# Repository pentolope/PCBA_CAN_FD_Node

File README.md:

# CAN-FD Sensor/Control Node

General-purpose CAN-FD node for a 24 V industrial system: MCU with CAN-FD, external transceiver, switchable termination, four inputs, four low-side outputs.

This repository holds the design problem for `PCBA_CAN_FD_Node`, titled in metadata "CAN-FD Sensor/Control Node": a general-purpose CAN-FD node for a 24 V industrial system. The brief fixes the functional skeleton: a modern MCU with CAN-FD driving an external CAN-FD transceiver, switchable 120-ohm bus termination, ESD protection at the bus connector, reverse-polarity and transient protection on the 24 V input, an efficient local regulator, and four digital inputs plus four low-side outputs for demonstration loads. It also fixes one placement rule — the CAN connector must place CANH/CANL adjacent, with protection and termination kept near that connector. Everything else is open: no part, vendor, connector, package, regulator topology, rail voltage, bit rate, current rating, board outline, or stackup is named, and the layer count is only characterised in metadata as "2 or 4". The design agent must choose and justify those, documenting engineering decisions rather than treating them as pre-existing user requirements.

> **This board has not been designed.** There is no schematic, no layout and no
> part selection here — only the brief, a reading of the brief, and the
> scaffolding a design run needs. That is the intended state of this repository,
> not a gap in it.

## What the brief fixes, and what it leaves open

The brief pins down 14 requirements and deliberately leaves
20 decisions to whoever designs the board. The `Source` column says
which is which: `brief` is quoted from [BRIEF.md](BRIEF.md), `metadata` comes
from the benchmark catalogue, and `open` means the brief does not fix it.

| Aspect | Value | Source |
|---|---|---|
| Board identity | repo PCBA_CAN_FD_Node; title "CAN-FD Sensor/Control Node"; benchmark_id 6 | metadata |
| Board function | General-purpose CAN-FD node for a 24 V industrial system | brief |
| Category / difficulty / brief detail | industrial-network; difficulty 2/5; detail 3/5 | metadata |
| Likely layer count | 2 or 4 | metadata |
| Primary stressors | CAN differential pair, 24V input protection, termination, MCU clocking | metadata |
| Controller | A modern MCU with CAN-FD (no family, part or package named) | brief |
| Bus PHY | External CAN-FD transceiver, separate from the MCU | brief |
| Bus termination | Switchable 120-ohm termination | brief |
| Bus protection | ESD protection at the bus connector | brief |
| 24 V input protection | Reverse-polarity and transient protection on the 24 V input | brief |
| Local power conversion | An efficient local regulator (topology, input source, rails and ratings unstated) | brief |
| Digital inputs | Four | brief |
| Outputs | Four low-side outputs, for demonstration loads | brief |
| CAN connector arrangement and protection zone | CANH/CANL adjacent at the connector; protection and termination kept near the connector | brief |
| Board outline, connector types, rails, bit rates and specific part numbers | Not fixed by the brief - design agent's choice | open |

The full split, with the verbatim brief text substantiating every fixed
requirement, is in [board/requirements.md](board/requirements.md) and
machine-readably in [board/requirements.json](board/requirements.json).

**Missing details are design freedom, not permission to fabricate unstated user
requirements.** A choice the brief left open is recorded as a decision, with its
reasoning — never promoted into a requirement.

## Benchmark position

| | |
|---|---|
| Benchmark id | 6 of 32 |
| Category | industrial-network |
| Difficulty | 2 / 5 |
| Brief detail | 3 / 5 |
| Likely layer count | 2 or 4 |
| Primary stressors | CAN differential pair, 24V input protection, termination, MCU clocking |

At difficulty 2/5 and brief detail 3/5 in the `industrial-network` category, this board tests whether an agent can execute a well-understood industrial node without over-claiming: the named stressors are the CAN differential pair, 24 V input protection, termination, and MCU clocking. The brief is specific about block-level content and one connector-region placement rule, but deliberately silent on parts, rails, bit rates, ratings, geometry and stackup — so the benchmark measures how cleanly an agent separates the stated architecture from the many unstated choices, and whether it can substantiate a differential pair, a protection front end, and a clock accurate enough for CAN-FD bit timing with real evidence rather than assertion.

This repository is one of thirty-two. The suite, the protocol and the results
live in [PCBA_AutoDesignAndTest_Bench](https://github.com/pentolope/PCBA_AutoDesignAndTest_Bench).

## Repository layout

| Path | Contents |
|---|---|
| `BRIEF.md` | the supplied brief — authoritative, preserved byte for byte, never edited |
| `board/requirements.md` | what the brief fixes, what it leaves open, and where decisions get recorded |
| `board/requirements.json` | the same split, machine-readable, each fixed requirement bound to brief text |
| `board/manifest.template.json` | the toolkit's minimum manifest, pre-filled for this board |
| `board/toolchain.json` | where this board's build finds KiCad and the router |
| `benchmark/metadata.json` | the supplied catalogue entry — category, difficulty, detail, stressors |
| `docs/architecture.md` | the decisions this board must make, as questions, unanswered |
| `docs/sources.md` | the classes of evidence the design will have to cite |
| `docs/status.md` | what exists, what does not, and what is deliberately absent |
| `candidates/` | disposable search output, ignored by Git |
| `.claude/skills/` | the accountability-review skill [CLAUDE.md](CLAUDE.md) requires before a push |
| `tooling/PCBA_AutoDesignAndTest` | the shared verification/routing/release toolkit, as a pinned submodule |

## Getting the repository

The toolkit is a submodule and carries KiCad Routing Tools as a submodule of its
own, so clone recursively:

```bash
git clone --recursive https://github.com/pentolope/PCBA_CAN_FD_Node.git
```

```bash
git submodule update --init --recursive
```

## Designing the board

Generic verification, routing and release logic is **not** written here. It is
consumed from `tooling/PCBA_AutoDesignAndTest`, which is board-agnostic by
construction and must stay that way; this repository owns the board and nothing
else. Start from
[the toolkit's onboarding guide](tooling/PCBA_AutoDesignAndTest/examples/onboarding.md),
and see [CLAUDE.md](CLAUDE.md) for the rules a design run works under.

```bash
python3 tooling/PCBA_AutoDesignAndTest/run.py preflight
```

## Brief integrity

`BRIEF.md` SHA-256 `3897ccfaae068a75cbd3eae3186d01ac4c7f7dafd298f4a1a979556b659bc86c`

Every quotation in `board/requirements.json` is bound to those exact bytes. If
the brief ever changes, the bindings are stale by construction — which is the
point of recording the digest.

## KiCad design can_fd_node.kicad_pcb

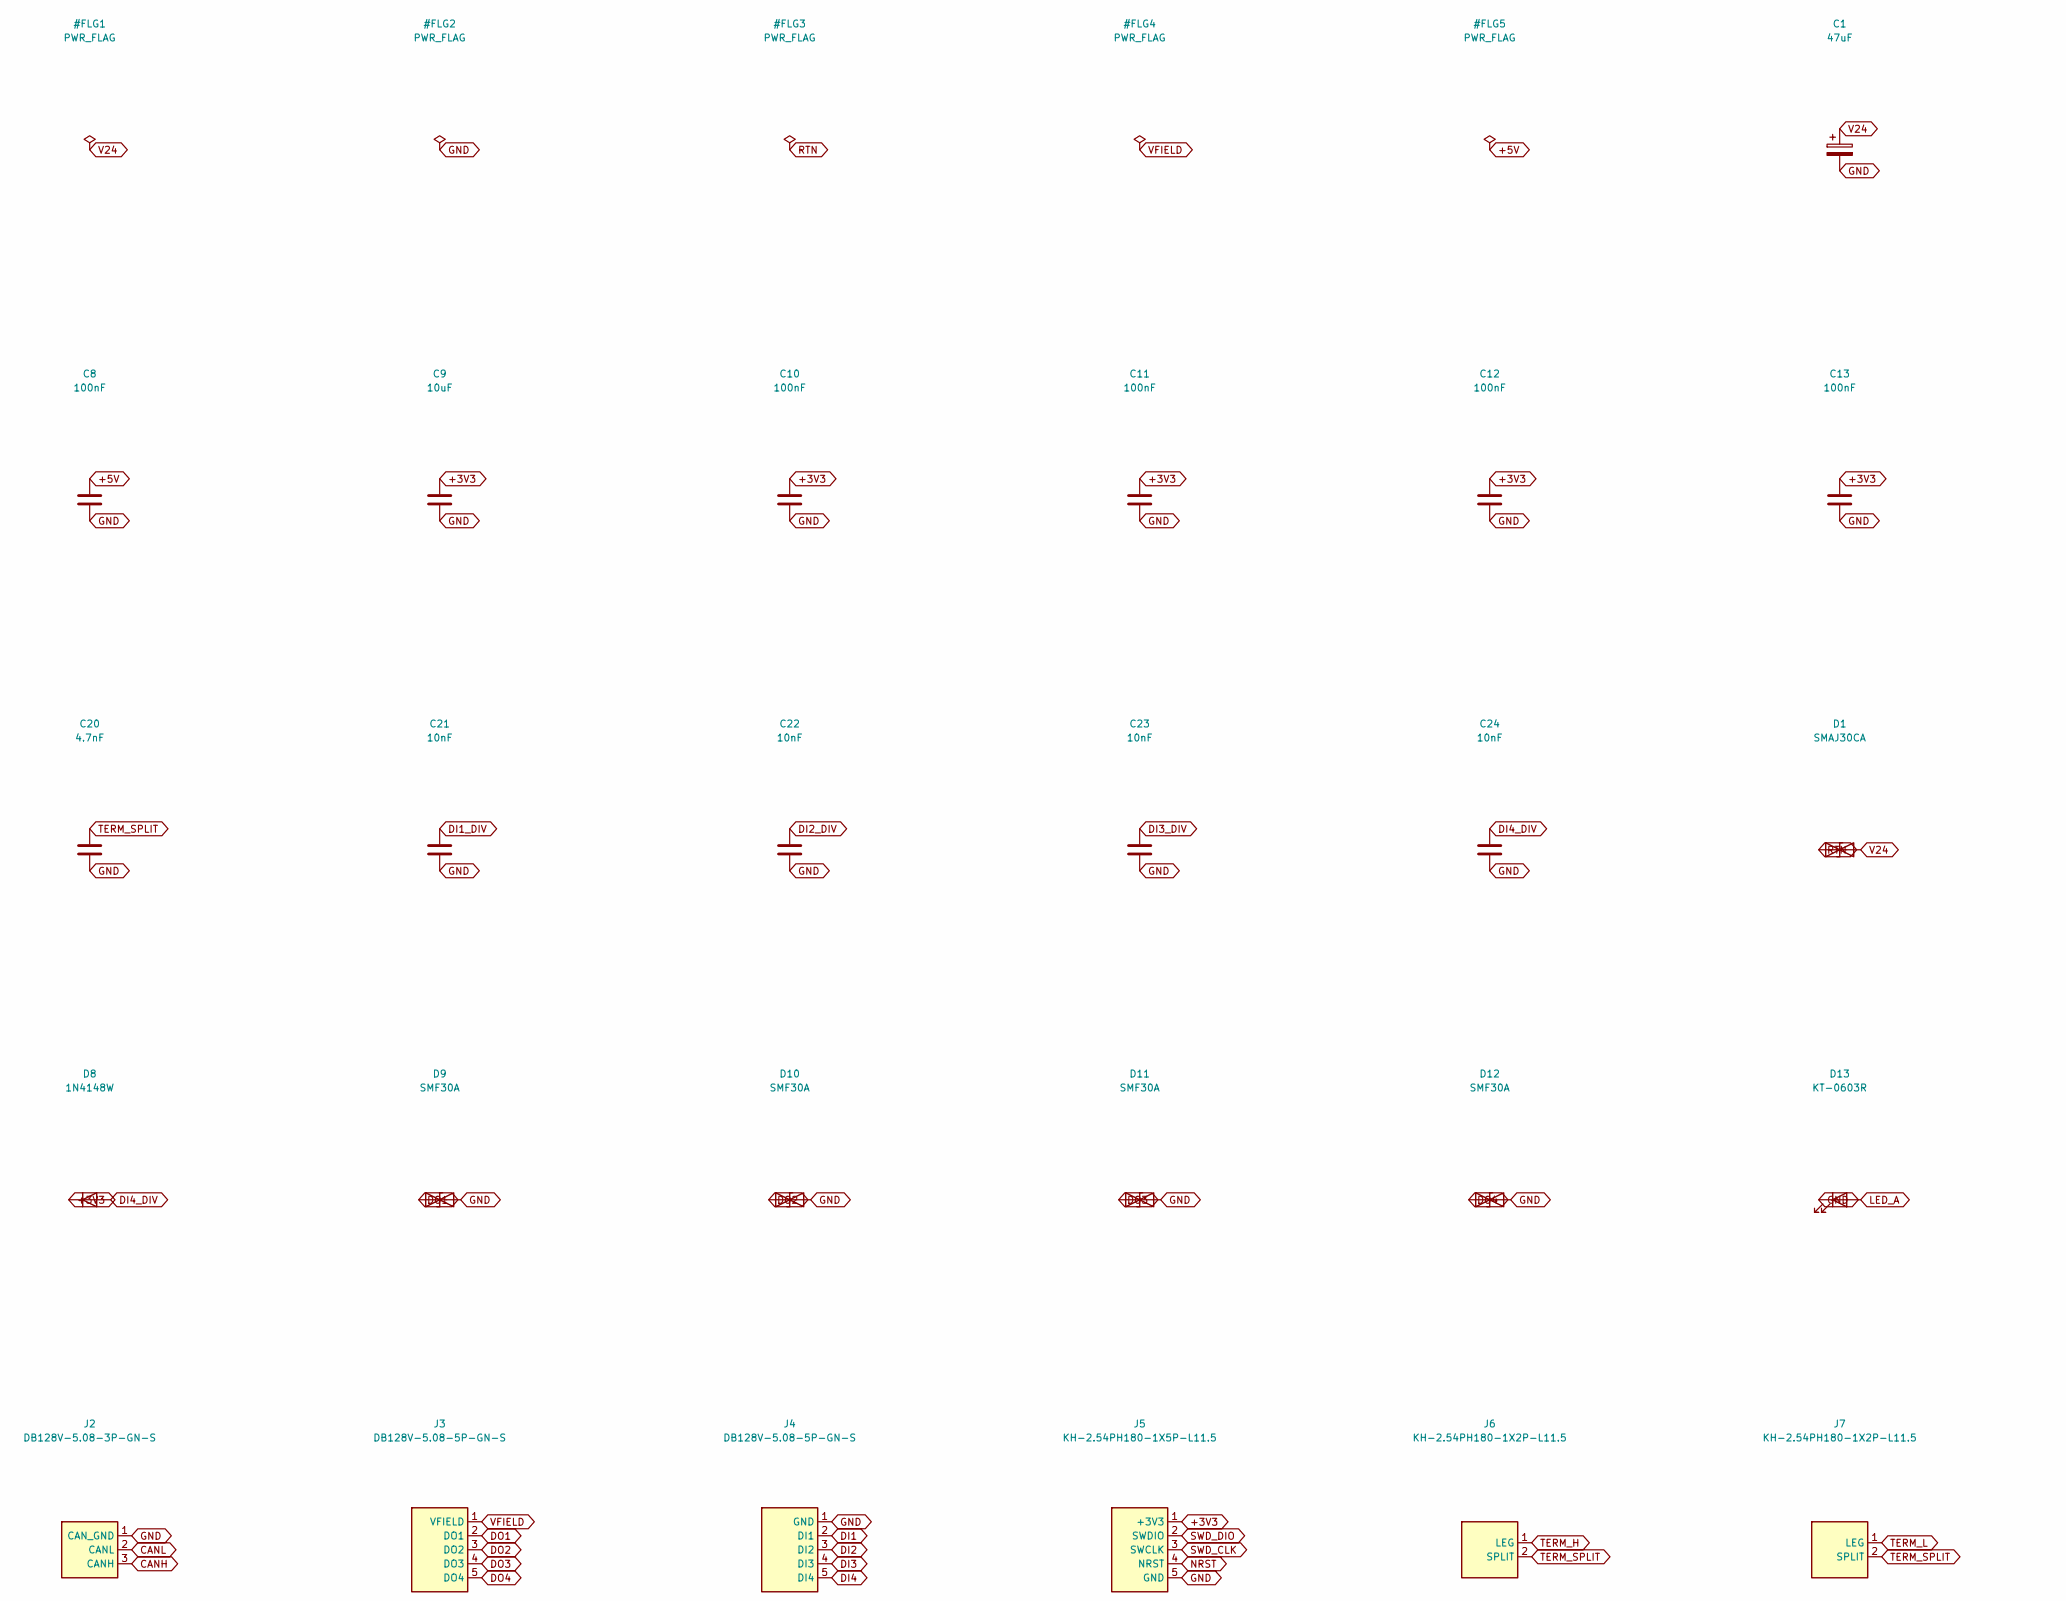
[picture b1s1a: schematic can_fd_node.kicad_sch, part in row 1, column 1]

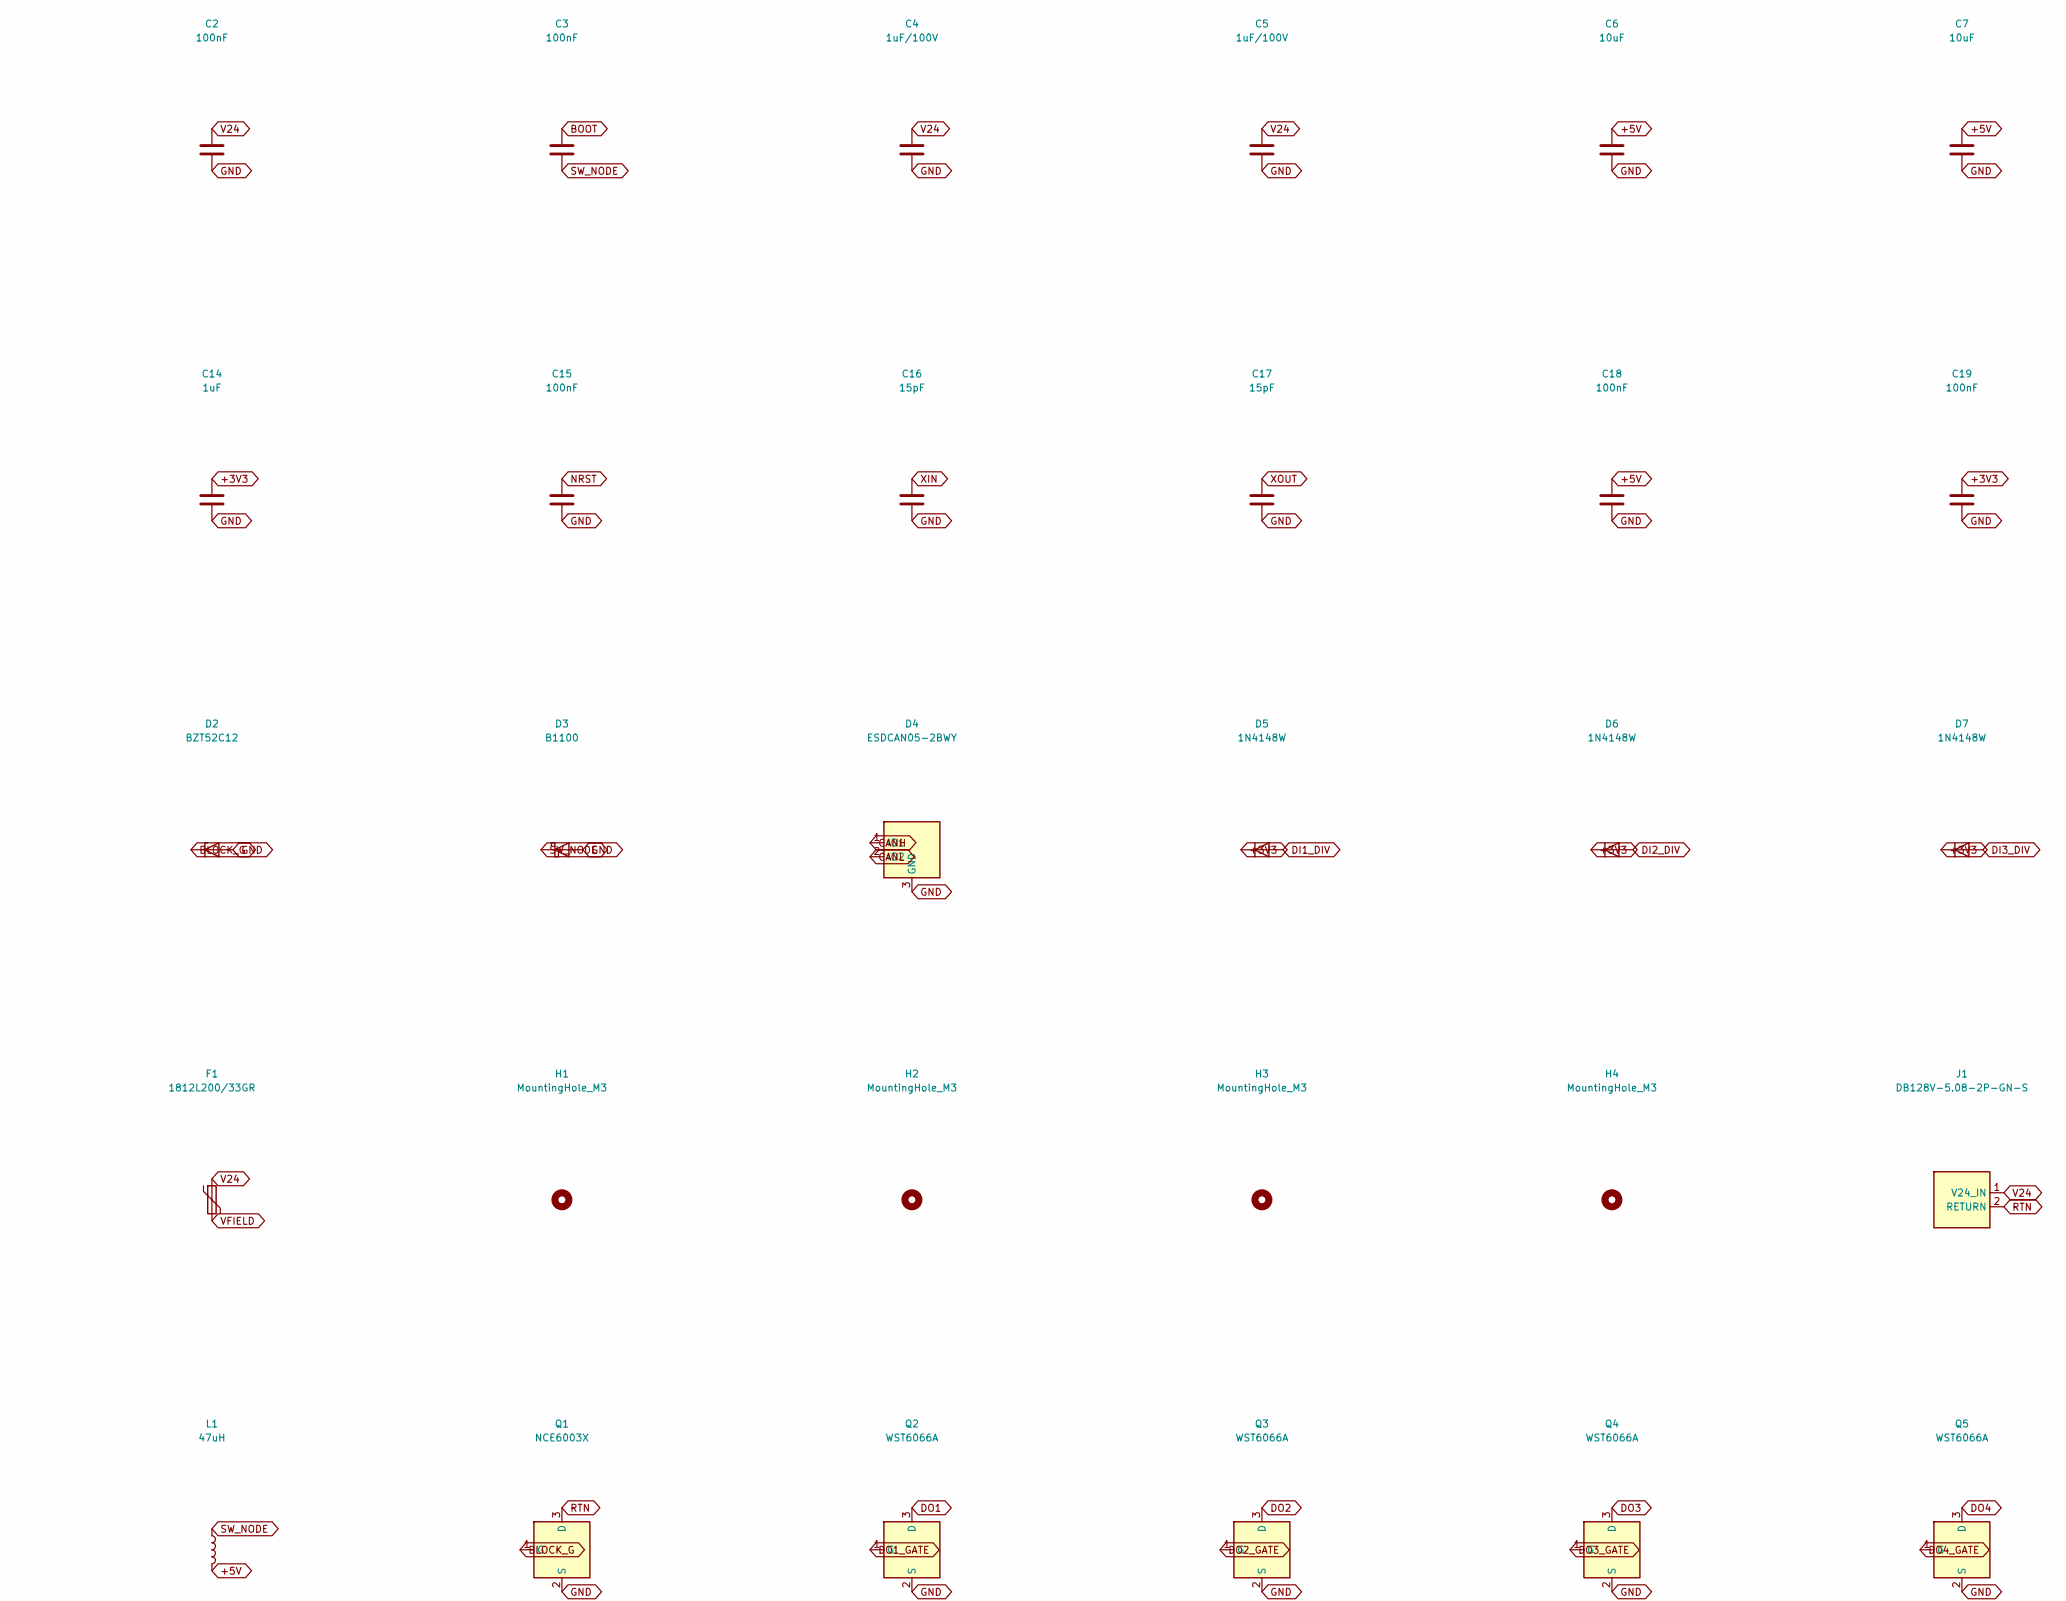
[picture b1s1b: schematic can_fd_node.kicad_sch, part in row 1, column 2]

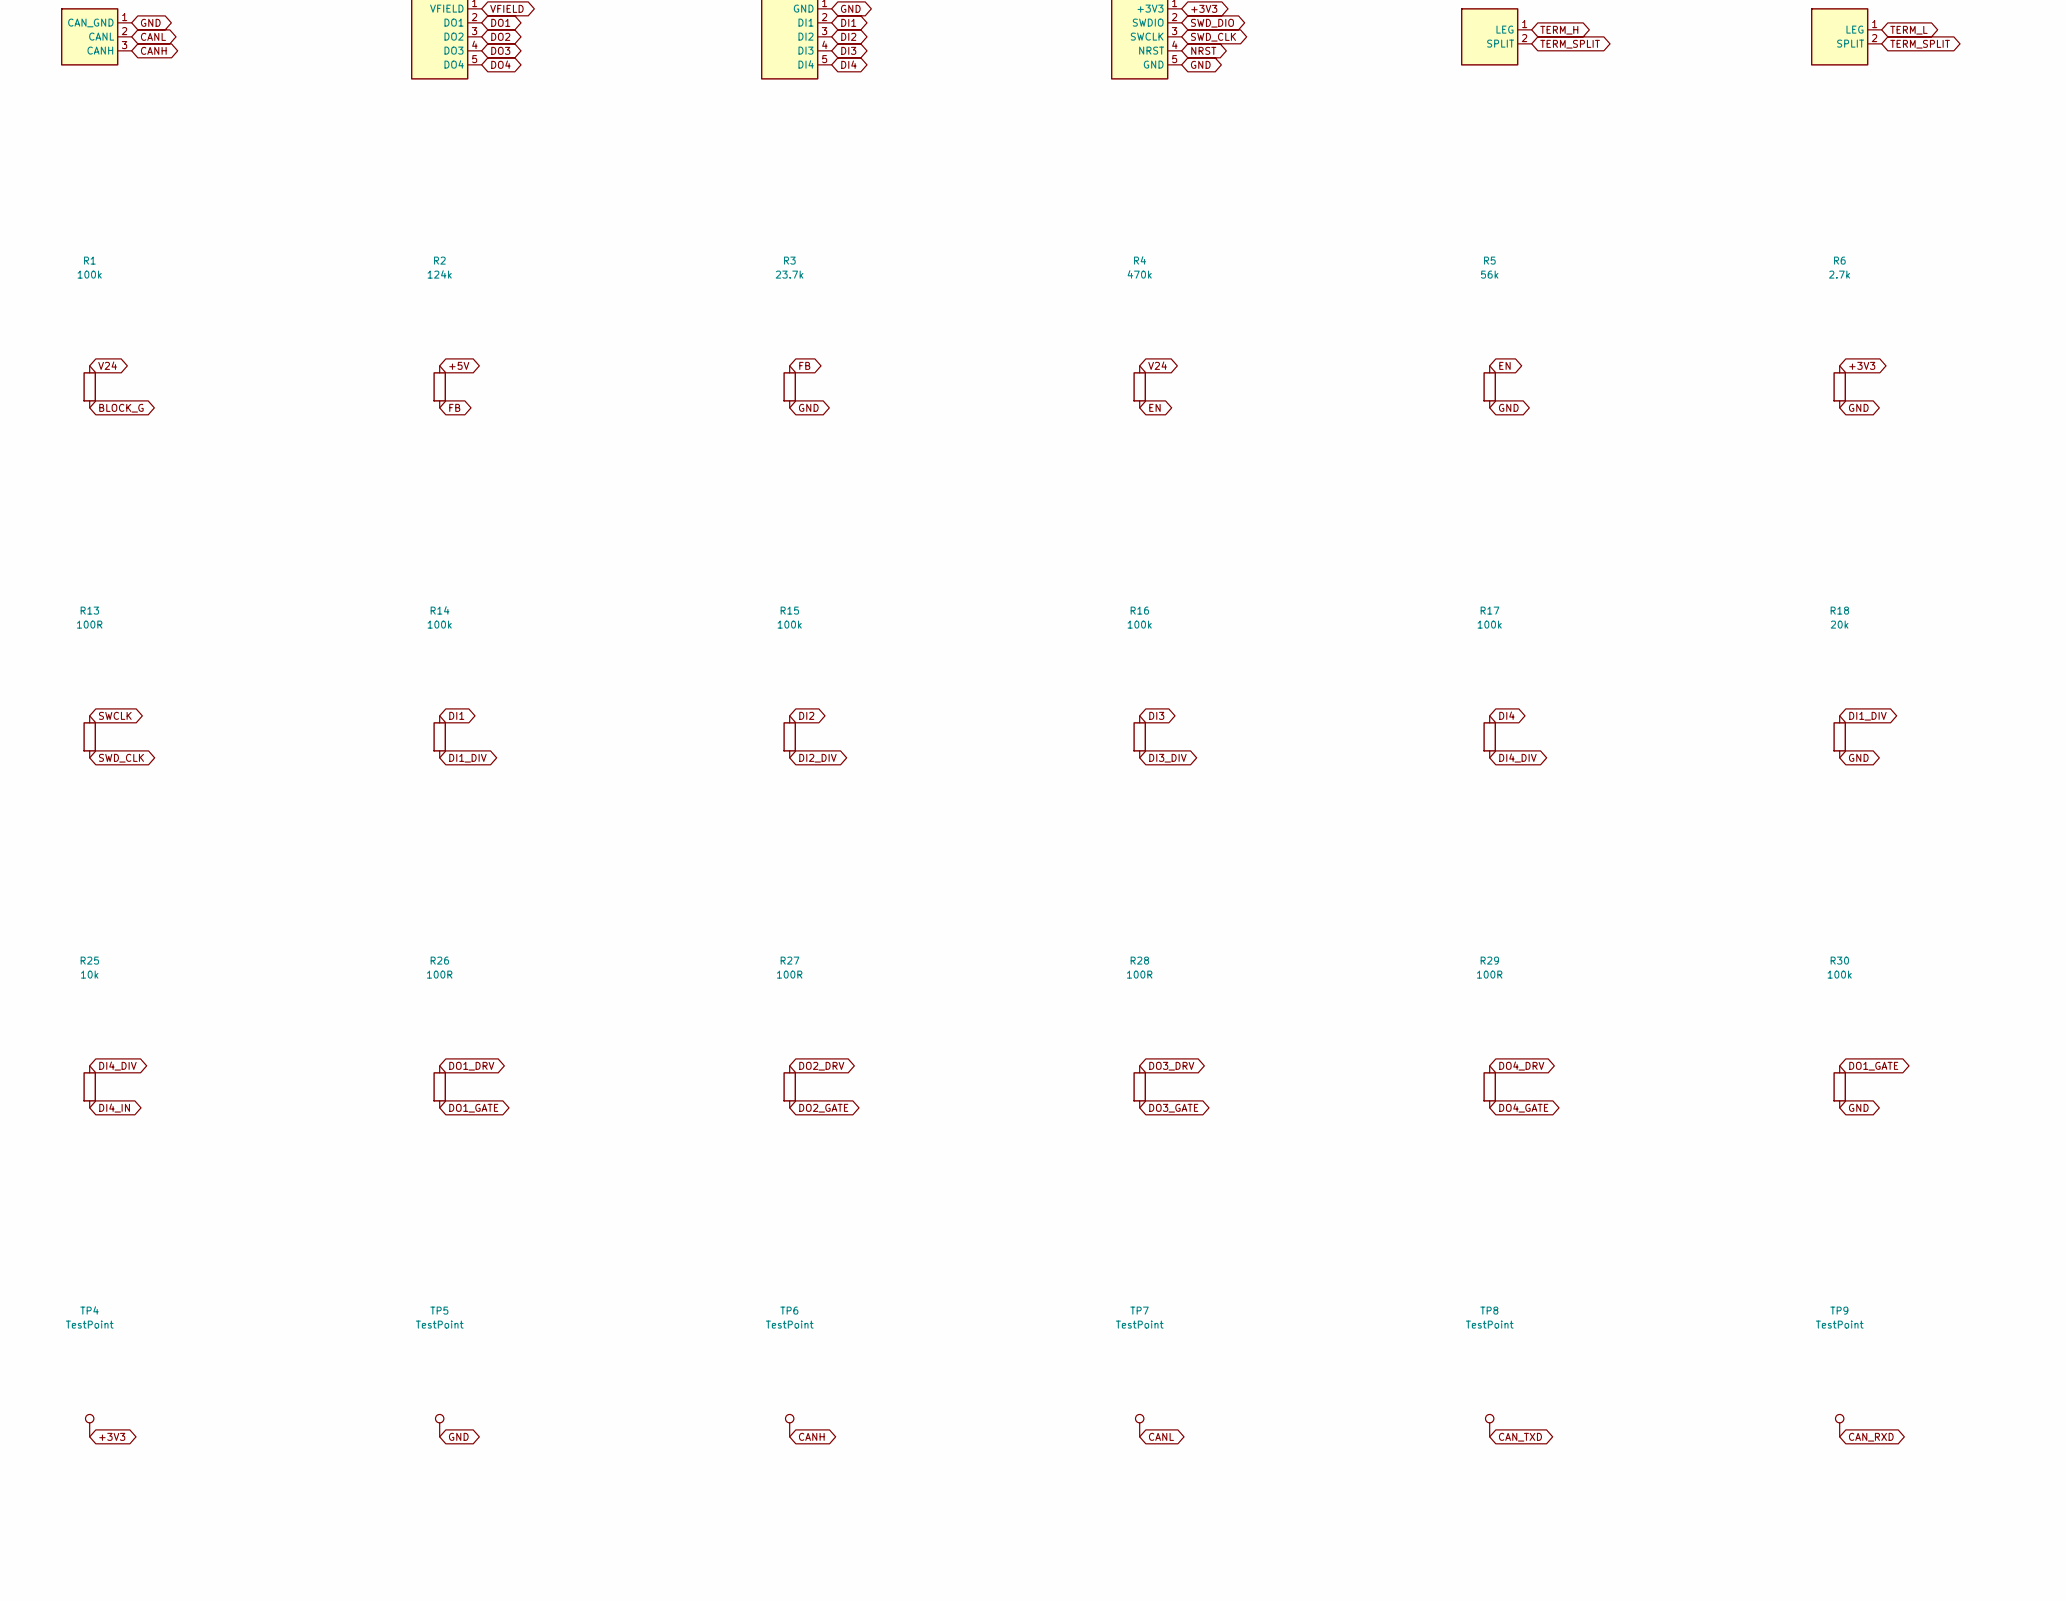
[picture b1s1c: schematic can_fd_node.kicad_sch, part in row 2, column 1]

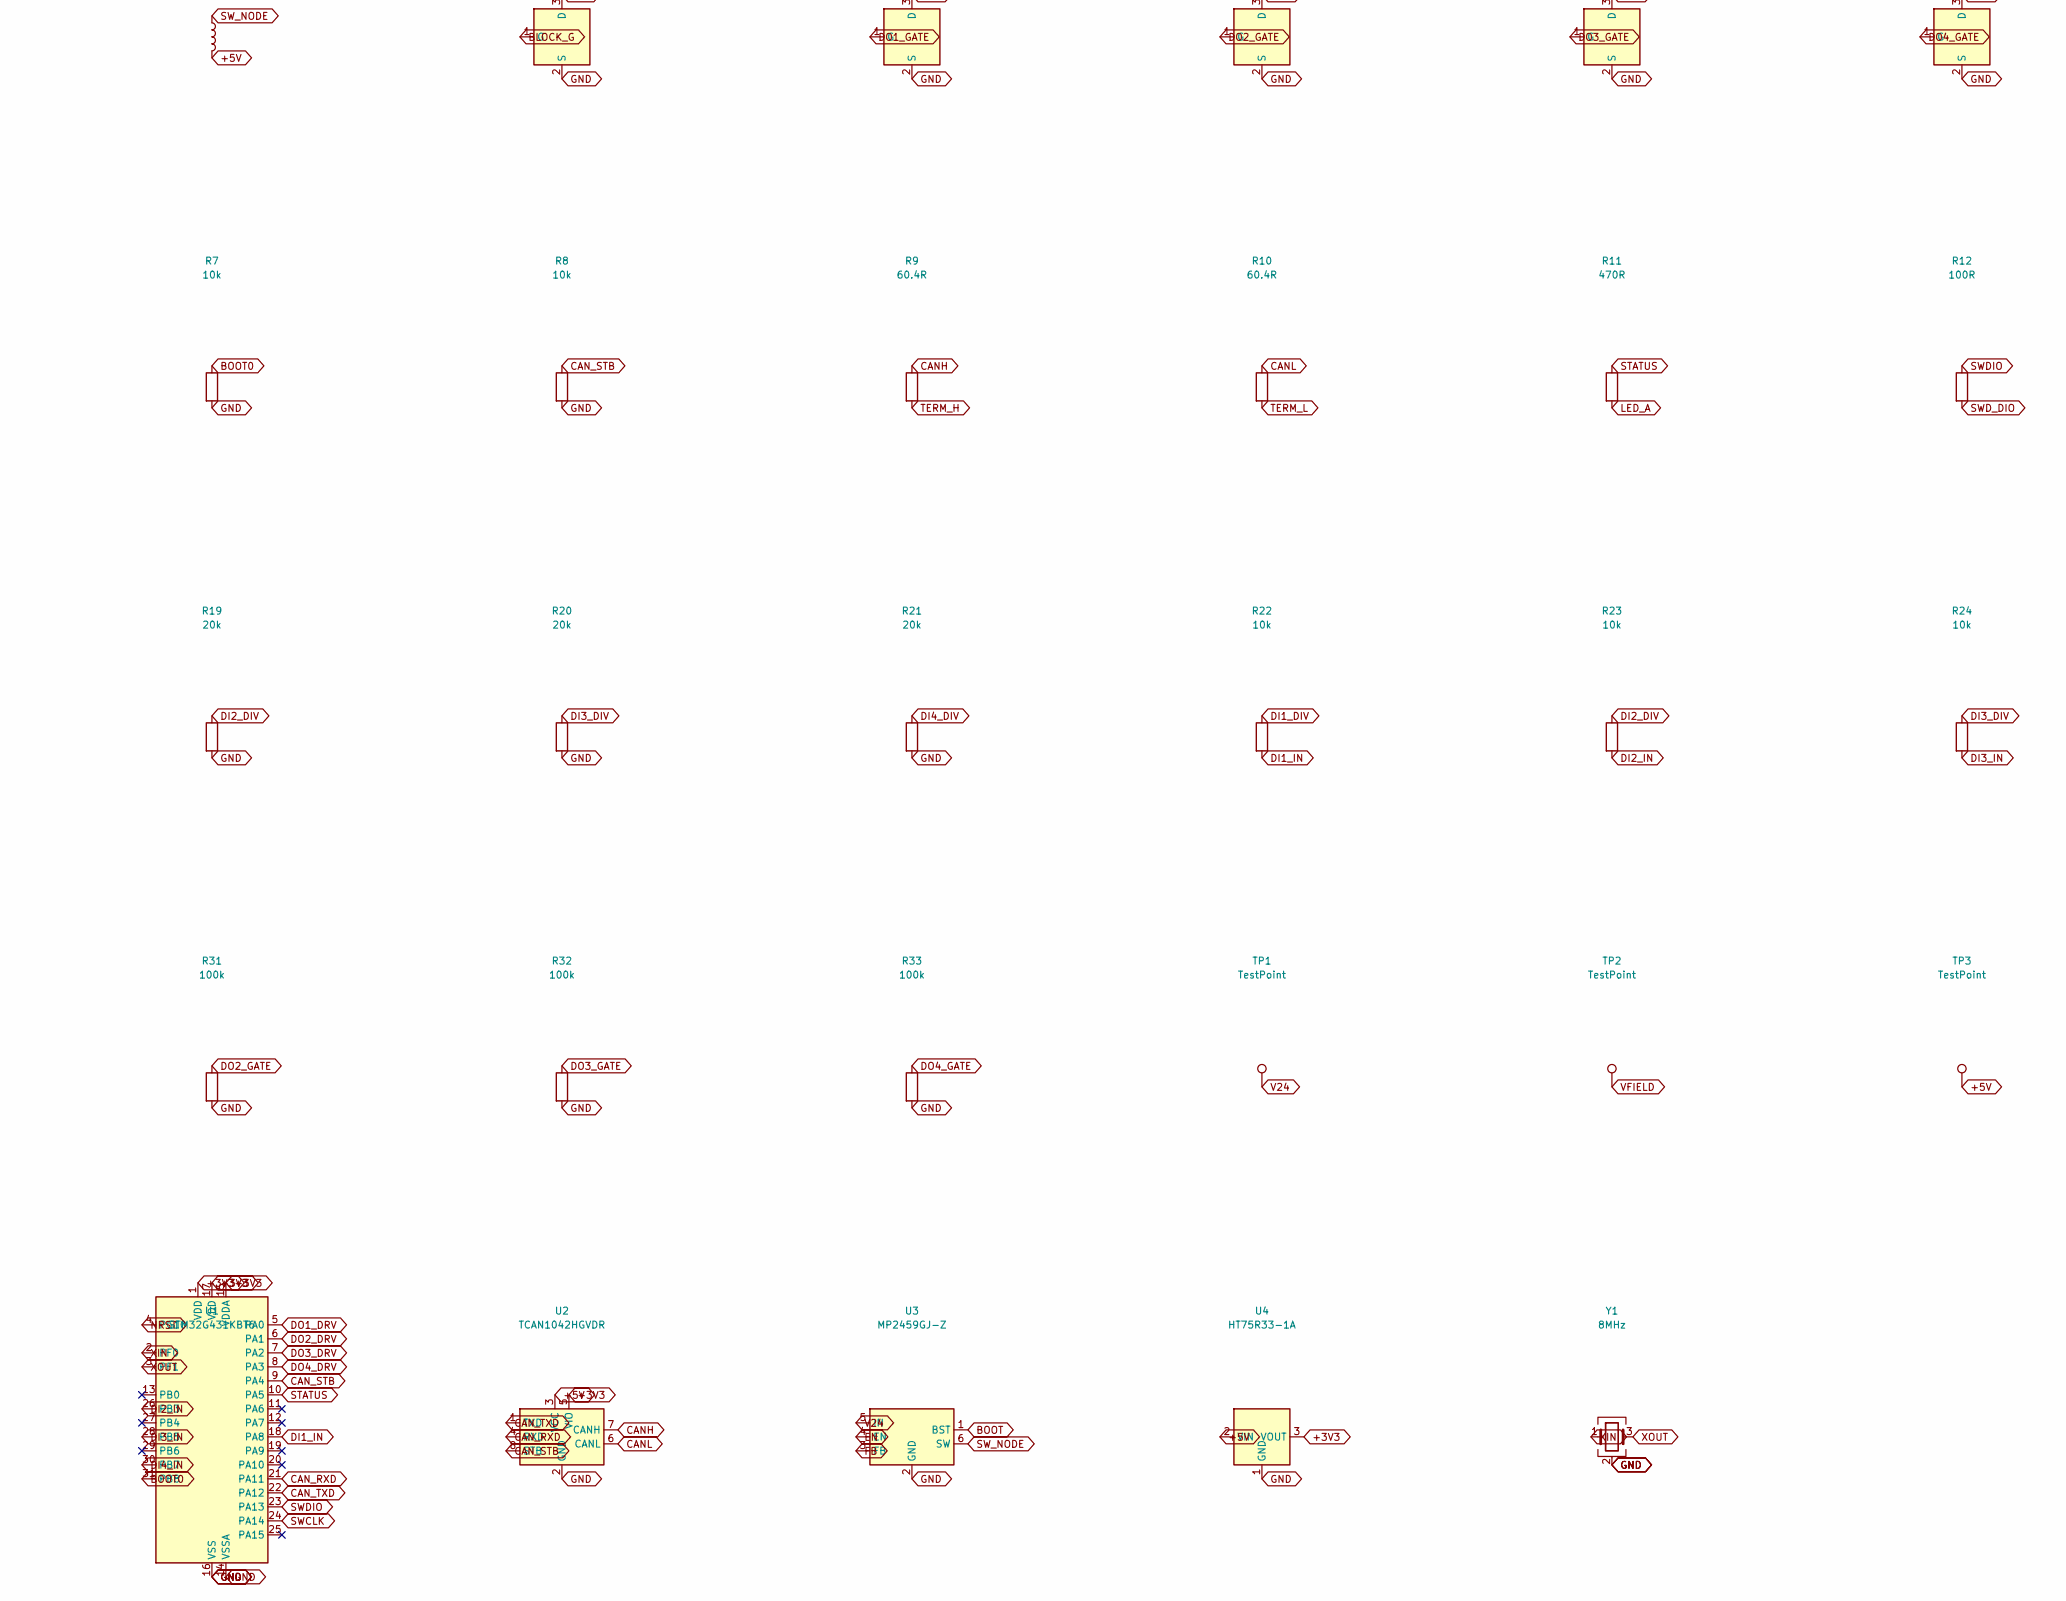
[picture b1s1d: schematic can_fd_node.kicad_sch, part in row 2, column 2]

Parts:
C1: 47uF; CP_Elec_6.3x7.7; MPN RVT63V47M6X8; LCSC C47023121
C2, C3, C8, C10, C11, C12, C13, C15, C18, C19: 100nF; C_0603_1608Metric; MPN CC0603KRX7R0BB104; LCSC C113803
C4, C5: 1uF/100V; C_1206_3216Metric; MPN CC1206KKX7R0BB105; LCSC C70463
C6, C7, C9: 10uF; C_0805_2012Metric; MPN CC0805KKX7R7BB106; LCSC C326595
C14: 1uF; C_0603_1608Metric; MPN CC0603KRX7R8BB105; LCSC C106858
C16, C17: 15pF; C_0603_1608Metric; MPN CC0603JRNPO9BN150; LCSC C107037
C20: 4.7nF; C_0603_1608Metric; MPN CC0603KRX7R0BB472; LCSC C115052
C21, C22, C23, C24: 10nF; C_0603_1608Metric; MPN CC0603KRX7R0BB103; LCSC C107059
D1: SMAJ30CA; D_SMA; MPN SMAJ30CA; LCSC C110043
D2: BZT52C12; D_SOD-123; MPN BZT52C12; LCSC C173429
D3: B1100; D_SMA; MPN B1100-13-F; LCSC C110106
D4: ESDCAN05-2BWY; SOT-323_SC-70; MPN ESDCAN05-2BWY; LCSC C1973137
D5, D6, D7, D8: 1N4148W; D_SOD-123; MPN 1N4148W; LCSC C81598
D9, D10, D11, D12: SMF30A; D_SOD-123FL_1.2x1.2mm_P3.2mm; MPN SMF30A; LCSC C364281
D13: KT-0603R; LED_0603_1608Metric; MPN KT-0603R; LCSC C2286
F1: 1812L200/33GR; PTC_1812_LUTE_1812L; MPN 1812L200/33GR; LCSC C18198343
H1, H2, H3, H4: MountingHole_M3; MountingHole_3.2mm_M3
J1: DB128V-5.08-2P-GN-S; TerminalBlock_DB128V-5.08_1x02_P5.08mm; MPN DB128V-5.08-2P-GN-S; LCSC C2915639
J2: DB128V-5.08-3P-GN-S; TerminalBlock_DB128V-5.08_1x03_P5.08mm; MPN DB128V-5.08-3P-GN-S; LCSC C2915640
J3, J4: DB128V-5.08-5P-GN-S; TerminalBlock_DB128V-5.08_1x05_P5.08mm; MPN DB128V-5.08-5P-GN-S; LCSC C2927513
J5: KH-2.54PH180-1X5P-L11.5; PinHeader_1x05_P2.54mm_Vertical; MPN KH-2.54PH180-1X5P-L11.5; LCSC C2932699
J6, J7: KH-2.54PH180-1X2P-L11.5; PinHeader_1x02_P2.54mm_Vertical; MPN KH-2.54PH180-1X2P-L11.5; LCSC C2905434
L1: 47uH; Inductor_Sunlord_SWPA5040; MPN SWPA5040S470MT; LCSC C86617
Q1: NCE6003X; SOT-23; MPN NCE6003X; LCSC C2934580
Q2, Q3, Q4, Q5: WST6066A; SOT-23; MPN WST6066A; LCSC C148352
R1, R14, R15, R16, R17, R30, R31, R32, R33: 100k; R_0603_1608Metric; MPN 0603WAF1003T5E; LCSC C25803
R2: 124k; R_0603_1608Metric; MPN 0603WAF1243T5E; LCSC C22788
R3: 23.7k; R_0603_1608Metric; MPN 0603WAF2372T5E; LCSC C22912
R4: 470k; R_0603_1608Metric; MPN 0603WAF4703T5E; LCSC C23178
R5: 56k; R_0603_1608Metric; MPN 0603WAF5602T5E; LCSC C23206
R6: 2.7k; R_0603_1608Metric; MPN 0603WAF2701T5E; LCSC C13167
R7, R8, R22, R23, R24, R25: 10k; R_0603_1608Metric; MPN 0603WAF1002T5E; LCSC C25804
R9, R10: 60.4R; R_2512_6332Metric; MPN RMCF2512FT60R4; LCSC C3994751
R11: 470R; R_0603_1608Metric; MPN 0603WAF4700T5E; LCSC C23179
R12, R13, R26, R27, R28, R29: 100R; R_0603_1608Metric; MPN 0603WAF1000T5E; LCSC C22775
R18, R19, R20, R21: 20k; R_0603_1608Metric; MPN 0603WAF2002T5E; LCSC C4184
TP1, TP2, TP3, TP4, TP5, TP6, TP7, TP8, TP9: TestPoint; TestPoint_Pad_D1.0mm
U1: STM32G431KBT6; LQFP-32_7x7mm_P0.8mm; MPN STM32G431KBT6; LCSC C529357
U2: TCAN1042HGVDR; SOIC-8_3.9x4.9mm_P1.27mm; MPN TCAN1042HGVDR; LCSC C124014
U3: MP2459GJ-Z; TSOT-23-6; MPN MP2459GJ-Z; LCSC C39578
U4: HT75R33-1A; SOT-89-3; MPN HT75R33-1A; LCSC C53223865
Y1: 8MHz; Crystal_YXC_YSX531SL_5.0x3.2mm; MPN XL1EL89CMI-111YLC-8M; LCSC C19711736

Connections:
+3V3: C9.1, C10.1, C11.1, C12.1, C13.1, C14.1, C19.1, D5.1 (K), D6.1 (K), D7.1 (K), D8.1 (K), J5.1 (+3V3), R6.1, TP4.1, U1.1 (VDD), U1.15 (VDDA), U1.17 (VDD), U2.5 (VIO), U4.3 (VOUT)
+5V: C6.1, C7.1, C8.1, C18.1, L1.2, R2.1, TP3.1, U2.3 (VCC), U4.2 (VIN)
BLOCK_G: D2.1 (K), Q1.1 (G), R1.2
BOOT: C3.1, U3.1 (BST)
BOOT0: R7.1, U1.31 (PB8)
CANH: D4.1 (IO1), J2.3 (CANH), R9.1, TP6.1, U2.7 (CANH)
CANL: D4.2 (IO2), J2.2 (CANL), R10.1, TP7.1, U2.6 (CANL)
CAN_RXD: TP9.1, U1.21 (PA11), U2.4 (RXD)
CAN_STB: R8.1, U1.9 (PA4), U2.8 (STB)
CAN_TXD: TP8.1, U1.22 (PA12), U2.1 (TXD)
DI1: J4.2 (DI1), R14.1
DI1_DIV: C21.1, D5.2 (A), R14.2, R18.1, R22.1
DI1_IN: R22.2, U1.18 (PA8)
DI2: J4.3 (DI2), R15.1
DI2_DIV: C22.1, D6.2 (A), R15.2, R19.1, R23.1
DI2_IN: R23.2, U1.26 (PB3)
DI3: J4.4 (DI3), R16.1
DI3_DIV: C23.1, D7.2 (A), R16.2, R20.1, R24.1
DI3_IN: R24.2, U1.28 (PB5)
DI4: J4.5 (DI4), R17.1
DI4_DIV: C24.1, D8.2 (A), R17.2, R21.1, R25.1
DI4_IN: R25.2, U1.30 (PB7)
DO1: D9.1 (A1), J3.2 (DO1), Q2.3 (D)
DO1_DRV: R26.1, U1.5 (PA0)
DO1_GATE: Q2.1 (G), R26.2, R30.1
DO2: D10.1 (A1), J3.3 (DO2), Q3.3 (D)
DO2_DRV: R27.1, U1.6 (PA1)
DO2_GATE: Q3.1 (G), R27.2, R31.1
DO3: D11.1 (A1), J3.4 (DO3), Q4.3 (D)
DO3_DRV: R28.1, U1.7 (PA2)
DO3_GATE: Q4.1 (G), R28.2, R32.1
DO4: D12.1 (A1), J3.5 (DO4), Q5.3 (D)
DO4_DRV: R29.1, U1.8 (PA3)
DO4_GATE: Q5.1 (G), R29.2, R33.1
EN: R4.2, R5.1, U3.4 (EN)
FB: R2.2, R3.1, U3.3 (FB)
GND: C1.2, C2.2, C4.2, C5.2, C6.2, C7.2, C8.2, C9.2, C10.2, C11.2, C12.2, C13.2, C14.2, C15.2, C16.2, C17.2, C18.2, C19.2, C20.2, C21.2, C22.2, C23.2, C24.2, D2.2 (A), D3.2 (A), D4.3 (GND), D9.2 (A2), D10.2 (A2), D11.2 (A2), D12.2 (A2), D13.1 (K), J2.1 (CAN_GND), J4.1 (GND), J5.5 (GND), Q1.2 (S), Q2.2 (S), Q3.2 (S), Q4.2 (S), Q5.2 (S), R3.2, R5.2, R6.2, R7.2, R8.2, R18.2, R19.2, R20.2, R21.2, R30.2, R31.2, R32.2, R33.2, TP5.1, U1.14 (VSSA), U1.16 (VSS), U1.32 (VSS), U2.2 (GND), U3.2 (GND), U4.1 (GND), Y1.2 (G), Y1.4 (G)
LED_A: D13.2 (A), R11.2
NRST: C15.1, J5.4 (NRST), U1.4 (PG10)
RTN: D1.1 (A1), J1.2 (RETURN), Q1.3 (D)
STATUS: R11.1, U1.10 (PA5)
SWCLK: R13.1, U1.24 (PA14)
SWDIO: R12.1, U1.23 (PA13)
SWD_CLK: J5.3 (SWCLK), R13.2
SWD_DIO: J5.2 (SWDIO), R12.2
SW_NODE: C3.2, D3.1 (K), L1.1, U3.6 (SW)
TERM_H: J6.1 (LEG), R9.2
TERM_L: J7.1 (LEG), R10.2
TERM_SPLIT: C20.1, J6.2 (SPLIT), J7.2 (SPLIT)
V24: C1.1, C2.1, C4.1, C5.1, D1.2 (A2), F1.1, J1.1 (V24_IN), R1.1, R4.1, TP1.1, U3.5 (IN)
VFIELD: F1.2, J3.1 (VFIELD), TP2.1
XIN: C16.1, U1.2 (PF0), Y1.1
XOUT: C17.1, U1.3 (PF1), Y1.3

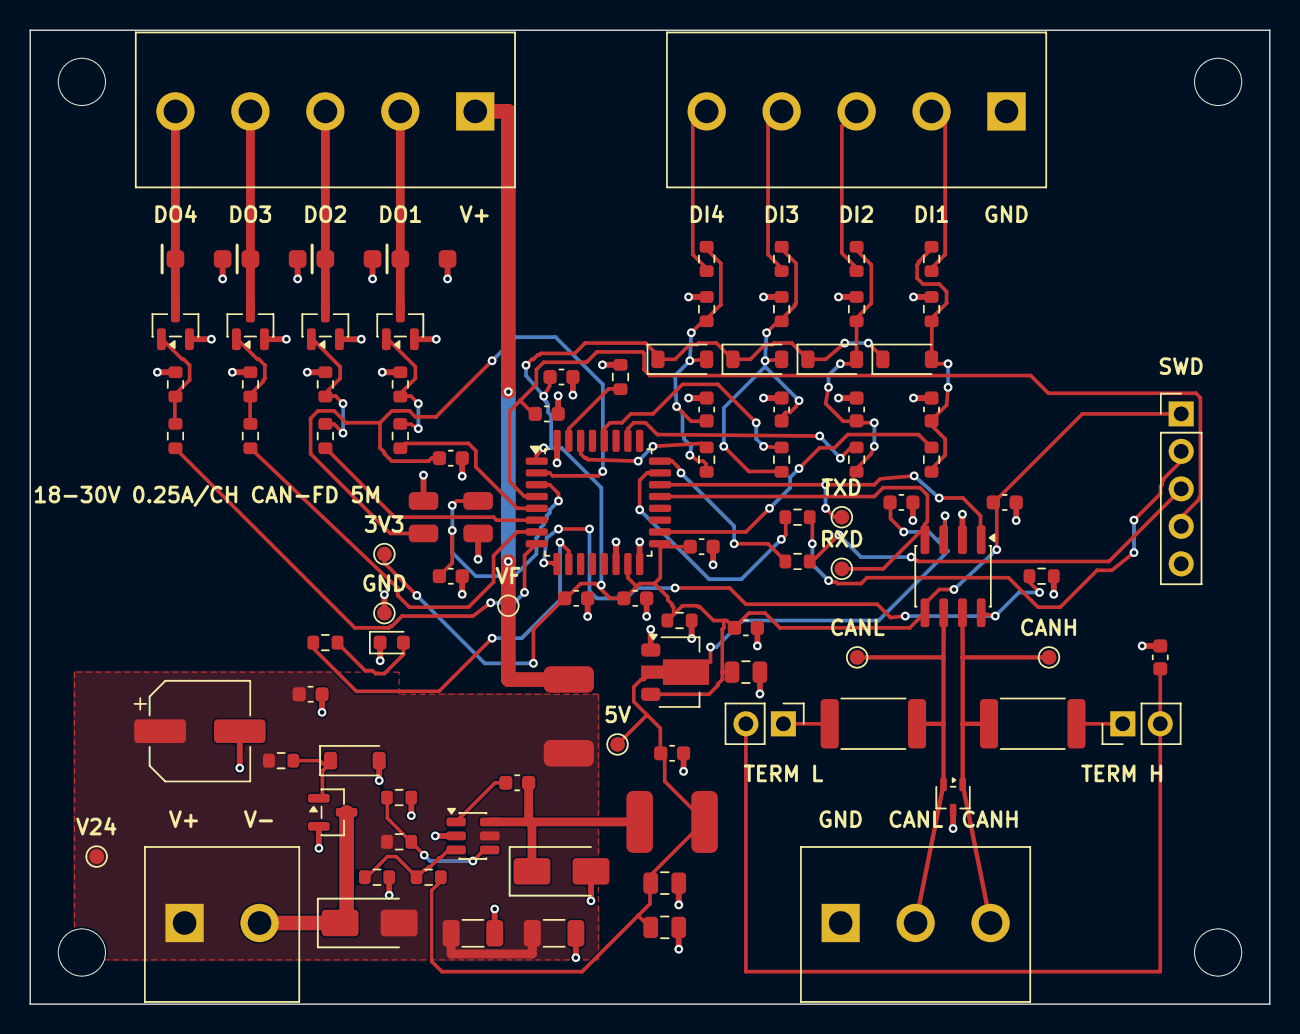
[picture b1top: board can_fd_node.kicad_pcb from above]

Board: 2 copper layers, 84.0 x 66.0 mm, 102 parts (0 on the bottom side), 53 nets.

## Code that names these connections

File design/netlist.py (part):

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#: What each of those pins is called and what peripheral it carries, so a
#: firmware author does not have to re-derive the mapping from the netlist.
MCU_PIN_FUNCTIONS = {
    "2": "PF0-OSC_IN", "3": "PF1-OSC_OUT", "4": "PG10-NRST",
    "5": "PA0", "6": "PA1", "7": "PA2", "8": "PA3", "9": "PA4",
    "10": "PA5", "18": "PA8", "21": "PA11/FDCAN1_RX",
    "22": "PA12/FDCAN1_TX", "23": "PA13/SWDIO", "24": "PA14/SWCLK",
    "26": "PB3", "28": "PB5", "30": "PB7", "31": "PB8-BOOT0",
}

#: Pins the LQFP-32 brings out that this board does not use.
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INTERMEDIATE_RAIL_NET = "+5V"
LOGIC_RAIL_NET = "+3V3"

#: Connector pin each function occupies. CANH and CANL are adjacent with
#: nothing between them, which the brief requires and the contract gate
#: checks.
CONNECTOR_FUNCTION_NETS = {
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        "EN": ["U3.4", "R4.2", "R5.1"],
        # controller
        "NRST": ["U1.%s" % RESET_PIN, "C15.1", "J5.4"],
        "XIN": ["U1.%s" % OSC_IN_PIN, "Y1.1", "C16.1"],
        "XOUT": ["U1.%s" % OSC_OUT_PIN, "Y1.3", "C17.1"],
        "BOOT0": ["U1.%s" % BOOT_PIN, "R7.1"],
        "STATUS": ["U1.%s" % STATUS_LED_PIN, "R11.1"],
        "SWDIO": ["U1.%s" % SWDIO_PIN, "R12.1"],
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        "SWD_CLK": ["R13.2", "J5.3"],
        "LED_A": ["R11.2", "D13.2"],
        # bus
        "CAN_TXD": ["U1.%s" % CAN_TX_PIN, "U2.1", "TP8.1"],
        "CAN_RXD": ["U1.%s" % CAN_RX_PIN, "U2.4", "TP9.1"],
        "CAN_STB": ["U1.%s" % TRANSCEIVER_STANDBY_PIN, "U2.8", "R8.1"],
        "CANH": ["J2.3", "D4.1", "R9.1", "U2.7", "TP6.1"],
        "CANL": ["J2.2", "D4.2", "R10.1", "U2.6", "TP7.1"],
        "TERM_H": ["R9.2", "J6.1"],
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
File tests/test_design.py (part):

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        self.assertEqual(carried[0], netlist.GROUND_NET)

    def test_the_termination_is_split_and_its_centre_is_decoupled(self):
        self.assertEqual(self.mapping["R9.1"], "CANH")
        self.assertEqual(self.mapping["R10.1"], "CANL")
        self.assertEqual(self.mapping["R9.2"], "TERM_H")
        self.assertEqual(self.mapping["R10.2"], "TERM_L")
        self.assertEqual(self.mapping["C20.1"], "TERM_SPLIT")
        self.assertEqual(self.mapping["C20.2"], netlist.GROUND_NET)

    def test_each_leg_carries_its_own_link_so_neither_half_is_stranded(self):
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        in that window; the controller only changes it afterwards.
        """
        self.assertEqual(self.mapping["R8.2"], netlist.GROUND_NET)
        self.assertEqual(self.mapping["R8.1"], "CAN_STB")
        self.assertEqual(self.mapping["U2.8"], "CAN_STB")
        self.assertEqual(
            self.mapping["U1.%s" % netlist.TRANSCEIVER_STANDBY_PIN],
            "CAN_STB")
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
